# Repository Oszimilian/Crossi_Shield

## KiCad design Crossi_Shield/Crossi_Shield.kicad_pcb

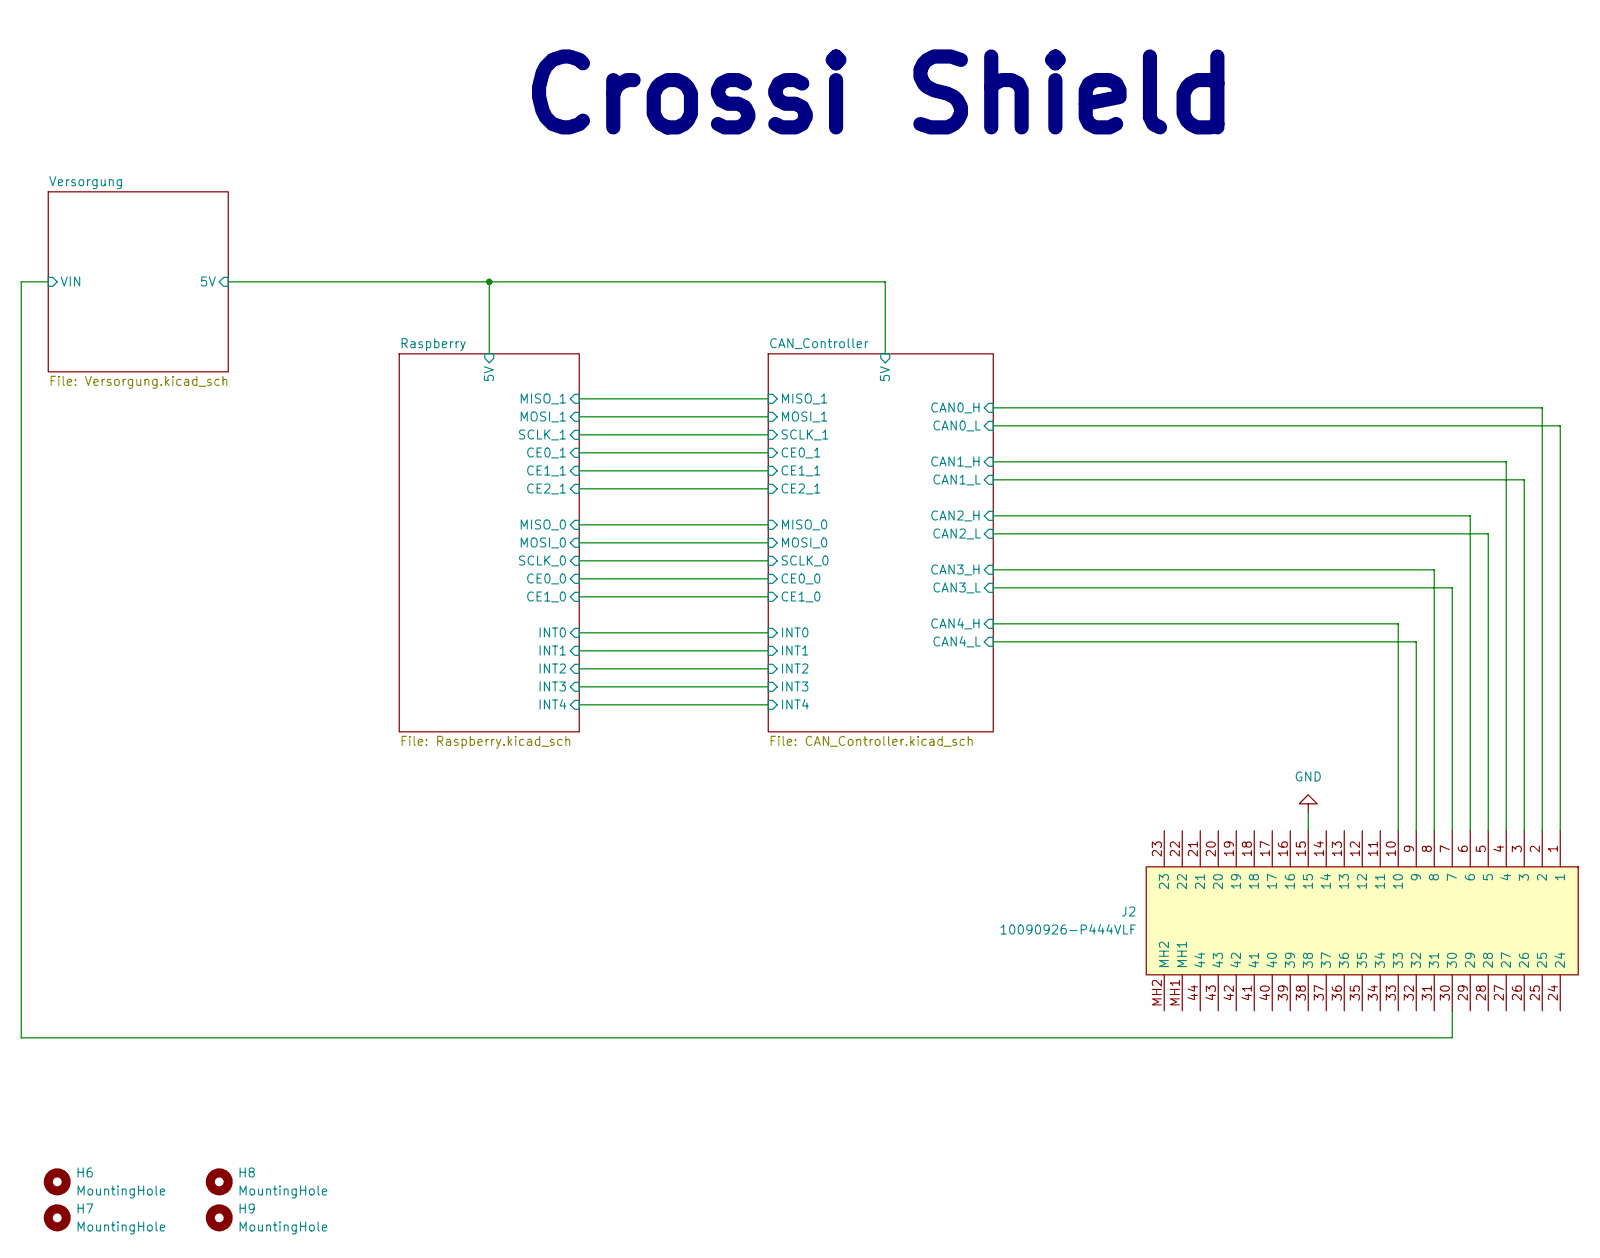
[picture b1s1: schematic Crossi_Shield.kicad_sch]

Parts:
H6, H7, H8, H9: MountingHole; MountingHole_3.2mm_M3_DIN965_Pad
J2: 10090926-P444VLF; 10090926P444VLF; Manufacturer_Part_Number 10090926-P444VLF; Mouser Part Number 649-10090926-P444VLF

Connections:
/CAN_Controller/CAN0_H: J2.2; also elsewhere on the board
/CAN_Controller/CAN0_L: J2.1; also elsewhere on the board
/CAN_Controller/CAN1_H: J2.4; also elsewhere on the board
/CAN_Controller/CAN1_L: J2.3; also elsewhere on the board
/CAN_Controller/CAN2_H: J2.6; also elsewhere on the board
/CAN_Controller/CAN2_L: J2.5; also elsewhere on the board
/CAN_Controller/CAN3_H: J2.8; also elsewhere on the board
/CAN_Controller/CAN3_L: J2.7; also elsewhere on the board
/CAN_Controller/CAN4_H: J2.10; also elsewhere on the board
/CAN_Controller/CAN4_L: J2.9; also elsewhere on the board
/Versorgung/VIN: J2.30; also elsewhere on the board
GND: J2.15; also elsewhere on the board

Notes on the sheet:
Crossi Shield

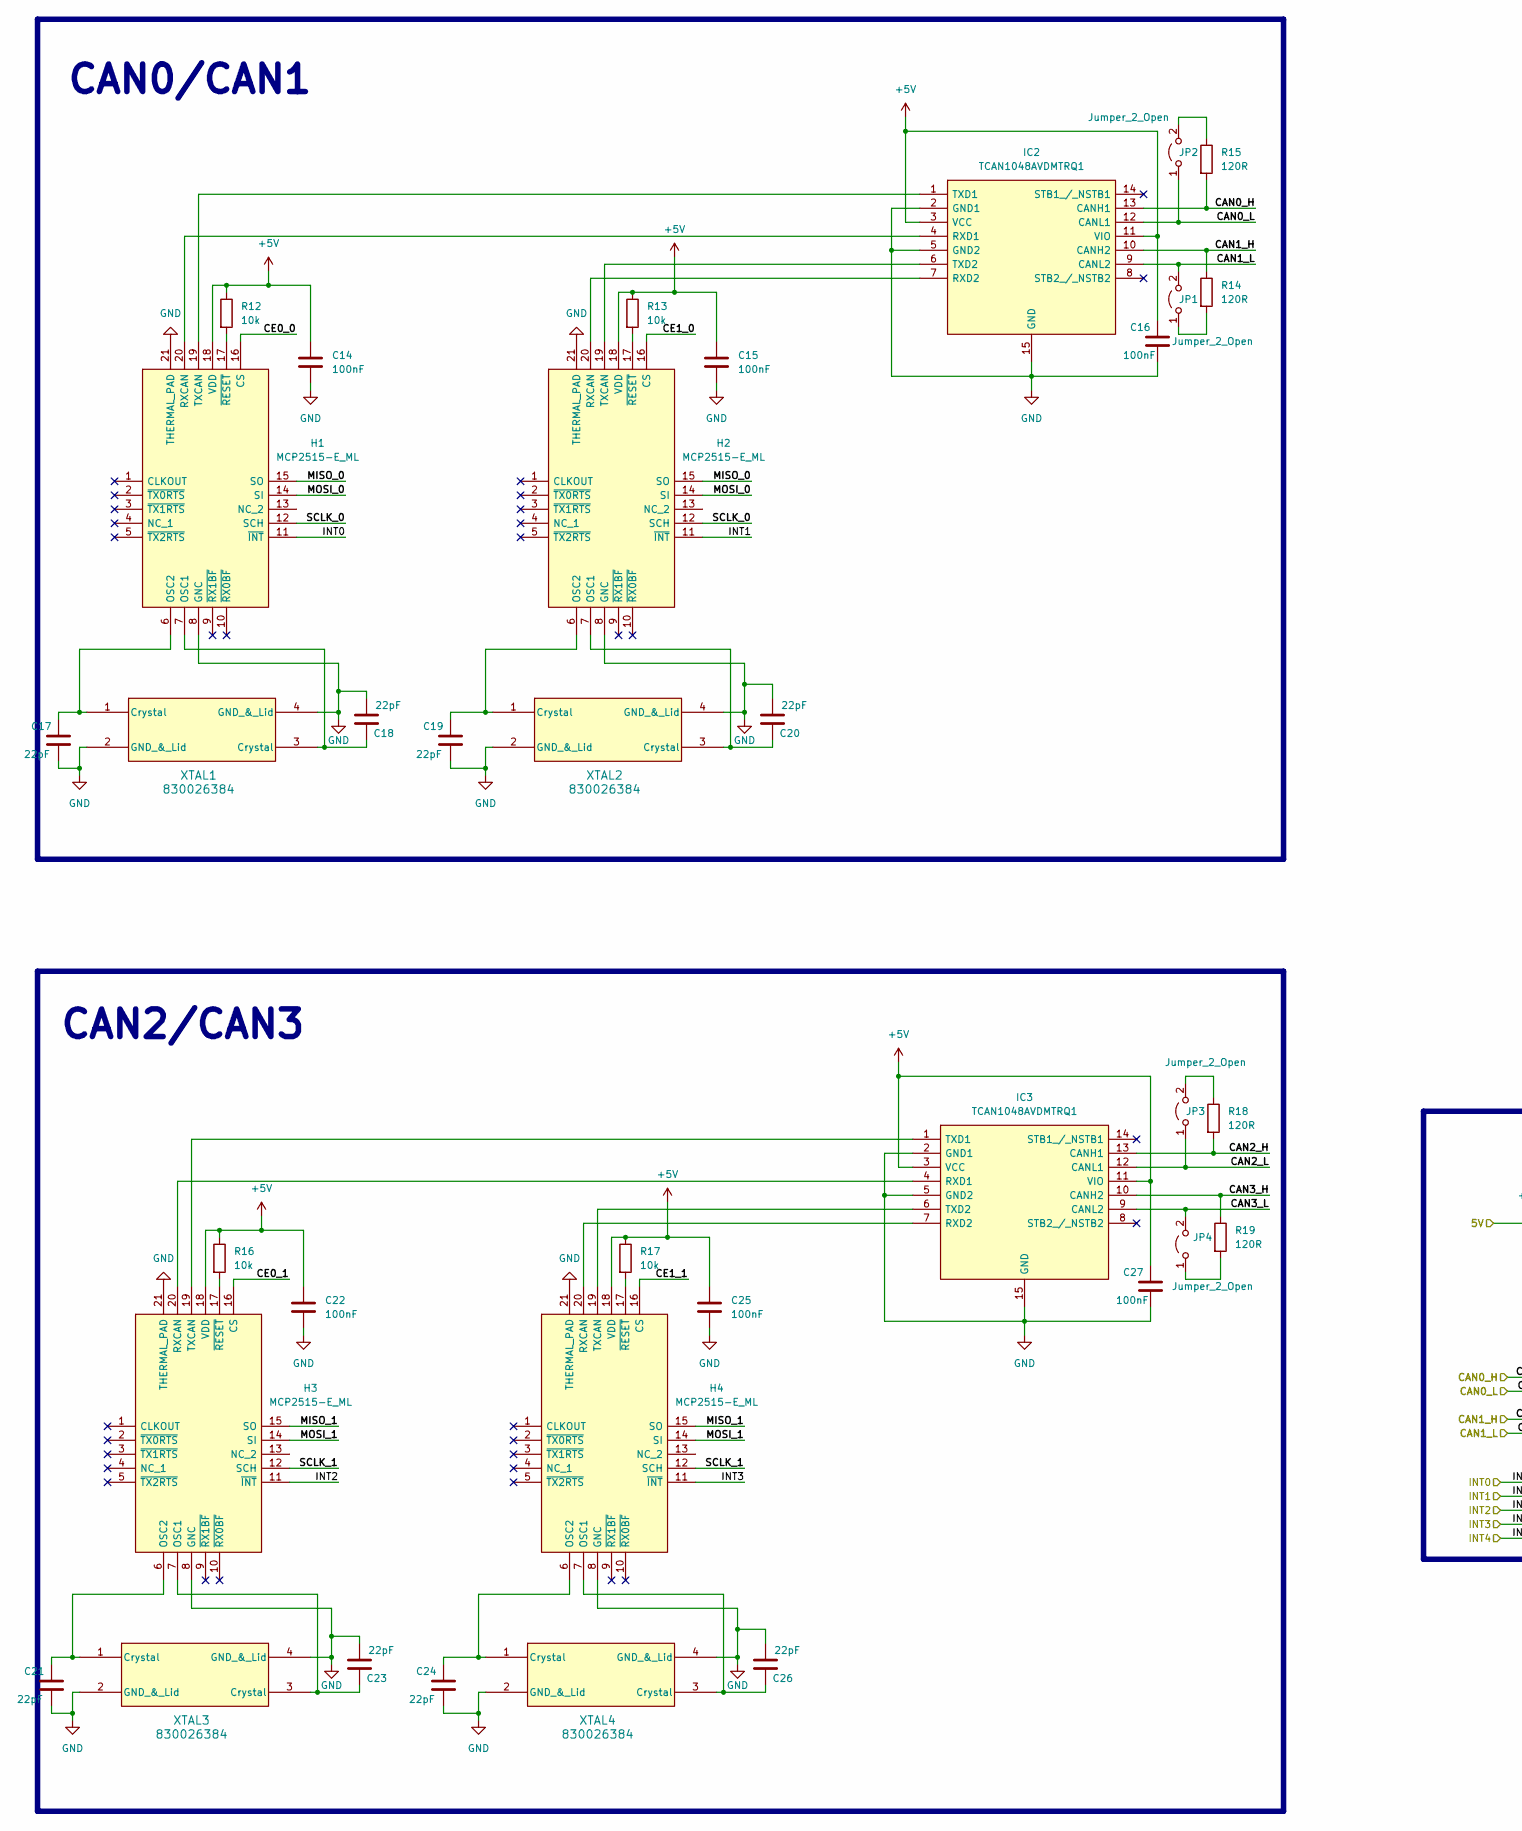
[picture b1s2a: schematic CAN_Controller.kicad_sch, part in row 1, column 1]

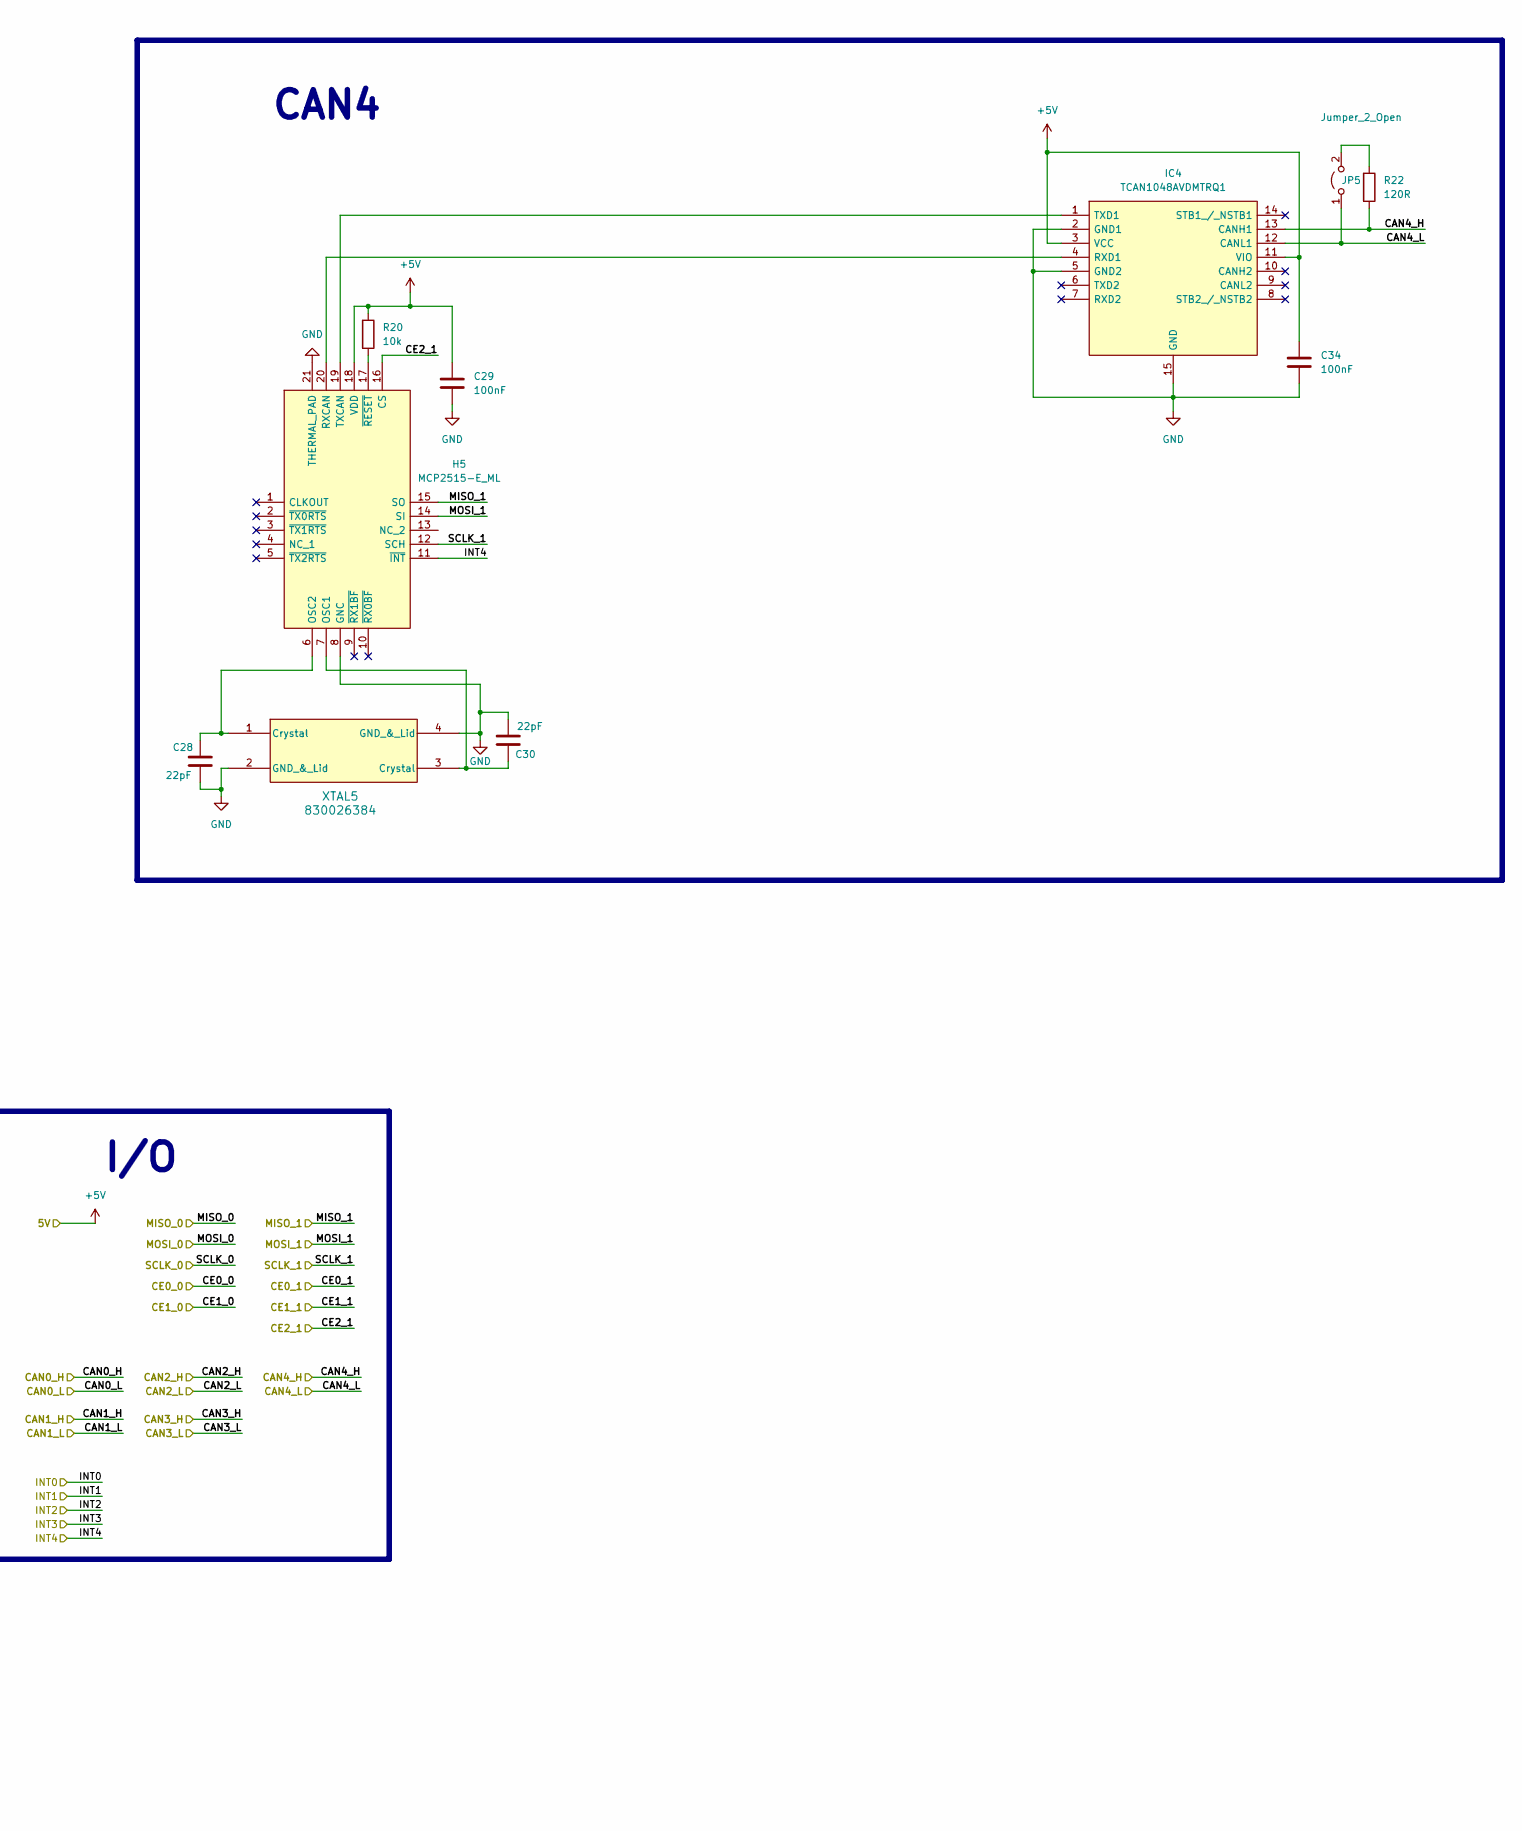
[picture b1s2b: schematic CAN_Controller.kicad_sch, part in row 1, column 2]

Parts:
C14, C15, C16, C22, C25, C27, C29, C34: 100nF; C_0805_2012Metric_Pad1.18x1.45mm_HandSolder
C17, C18, C19, C20, C21, C23, C24, C26, C28, C30: 22pF; C_0805_2012Metric_Pad1.18x1.45mm_HandSolder
H1, H2, H3, H4, H5: MCP2515-E_ML; QFN50P400X400X90-21N-D; Manufacturer_Part_Number MCP2515-E/ML; Mouser Part Number 579-MCP2515-E/ML
IC2, IC3, IC4: TCAN1048AVDMTRQ1; SON65P300X450X100-15N-D; Manufacturer_Part_Number TCAN1048AVDMTRQ1; Mouser Part Number 595-TCAN1048AVDMTRQ1
JP1, JP2, JP3, JP4, JP5: Jumper_2_Open; SolderJumper-2_P1.3mm_Open_RoundedPad1.0x1.5mm
R12, R13, R16, R17, R20: 10k; R_0805_2012Metric_Pad1.20x1.40mm_HandSolder
R14, R15, R18, R19, R22: 120R; R_0805_2012Metric_Pad1.20x1.40mm_HandSolder
XTAL1, XTAL2, XTAL3, XTAL4, XTAL5: 830026384; SMT_026384_WRE-L

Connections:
+5V: C14.1, C15.1, C16.1, C22.1, C25.1, C27.1, C29.1, C34.1, H1.18 (VDD), H2.18 (VDD), H3.18 (VDD), H4.18 (VDD), H5.18 (VDD), IC2.3 (VCC), IC2.11 (VIO), IC3.3 (VCC), IC3.11 (VIO), IC4.3 (VCC), IC4.11 (VIO), R12.1, R13.1, R16.1, R17.1, R20.1; also elsewhere on the board
/CAN_Controller/CAN0_H: IC2.13 (CANH1), R15.2; also elsewhere on the board
/CAN_Controller/CAN0_L: IC2.12 (CANL1), JP2.1 (A); also elsewhere on the board
/CAN_Controller/CAN1_H: IC2.10 (CANH2), R14.1; also elsewhere on the board
/CAN_Controller/CAN1_L: IC2.9 (CANL2), JP1.2 (B); also elsewhere on the board
/CAN_Controller/CAN2_H: IC3.13 (CANH1), R18.2; also elsewhere on the board
/CAN_Controller/CAN2_L: IC3.12 (CANL1), JP3.1 (A); also elsewhere on the board
/CAN_Controller/CAN3_H: IC3.10 (CANH2), R19.1; also elsewhere on the board
/CAN_Controller/CAN3_L: IC3.9 (CANL2), JP4.2 (B); also elsewhere on the board
/CAN_Controller/CAN4_H: IC4.13 (CANH1), R22.2; also elsewhere on the board
/CAN_Controller/CAN4_L: IC4.12 (CANL1), JP5.1 (A); also elsewhere on the board
/CAN_Controller/CE0_0: H1.16 (CS); also elsewhere on the board
/CAN_Controller/CE0_1: H3.16 (CS); also elsewhere on the board
/CAN_Controller/CE1_0: H2.16 (CS); also elsewhere on the board
/CAN_Controller/CE1_1: H4.16 (CS); also elsewhere on the board
/CAN_Controller/CE2_1: H5.16 (CS); also elsewhere on the board
/CAN_Controller/INT0: H1.11 (~INT); also elsewhere on the board
/CAN_Controller/INT1: H2.11 (~INT); also elsewhere on the board
/CAN_Controller/INT2: H3.11 (~INT); also elsewhere on the board
/CAN_Controller/INT3: H4.11 (~INT); also elsewhere on the board
/CAN_Controller/INT4: H5.11 (~INT); also elsewhere on the board
/CAN_Controller/MISO_0: H1.15 (SO), H2.15 (SO); also elsewhere on the board
/CAN_Controller/MISO_1: H3.15 (SO), H4.15 (SO), H5.15 (SO); also elsewhere on the board
/CAN_Controller/MOSI_0: H1.14 (SI), H2.14 (SI); also elsewhere on the board
/CAN_Controller/MOSI_1: H3.14 (SI), H4.14 (SI), H5.14 (SI); also elsewhere on the board
/CAN_Controller/SCLK_0: H1.12 (SCH), H2.12 (SCH); also elsewhere on the board
/CAN_Controller/SCLK_1: H3.12 (SCH), H4.12 (SCH), H5.12 (SCH); also elsewhere on the board
GND: C14.2, C15.2, C16.2, C17.2, C18.2, C19.2, C20.2, C21.2, C22.2, C23.2, C24.2, C25.2, C26.2, C27.2, C28.2, C29.2, C30.2, C34.2, H1.8 (GNC), H1.21 (THERMAL_PAD), H2.8 (GNC), H2.21 (THERMAL_PAD), H3.8 (GNC), H3.21 (THERMAL_PAD), H4.8 (GNC), H4.21 (THERMAL_PAD), H5.8 (GNC), H5.21 (THERMAL_PAD), IC2.2 (GND1), IC2.5 (GND2), IC2.15 (GND), IC3.2 (GND1), IC3.5 (GND2), IC3.15 (GND), IC4.2 (GND1), IC4.5 (GND2), IC4.15 (GND), XTAL1.2 (GND_&_Lid), XTAL1.4 (GND_&_Lid), XTAL2.2 (GND_&_Lid), XTAL2.4 (GND_&_Lid), XTAL3.2 (GND_&_Lid), XTAL3.4 (GND_&_Lid), XTAL4.2 (GND_&_Lid), XTAL4.4 (GND_&_Lid), XTAL5.2 (GND_&_Lid), XTAL5.4 (GND_&_Lid); also elsewhere on the board
unnamed: C18.1, H1.7 (OSC1), XTAL1.3 (Crystal)
unnamed: C17.1, H1.6 (OSC2), XTAL1.1 (Crystal)
unnamed: H1.20 (RXCAN), IC2.4 (RXD1)
unnamed: H1.19 (TXCAN), IC2.1 (TXD1)
unnamed: H1.17 (~RESET), R12.2
unnamed: C20.1, H2.7 (OSC1), XTAL2.3 (Crystal)
unnamed: C19.1, H2.6 (OSC2), XTAL2.1 (Crystal)
unnamed: H2.20 (RXCAN), IC2.7 (RXD2)
unnamed: H2.19 (TXCAN), IC2.6 (TXD2)
unnamed: H2.17 (~RESET), R13.2
unnamed: C23.1, H3.7 (OSC1), XTAL3.3 (Crystal)
unnamed: C21.1, H3.6 (OSC2), XTAL3.1 (Crystal)
unnamed: H3.20 (RXCAN), IC3.4 (RXD1)
unnamed: H3.19 (TXCAN), IC3.1 (TXD1)
unnamed: H3.17 (~RESET), R16.2
unnamed: C26.1, H4.7 (OSC1), XTAL4.3 (Crystal)
unnamed: C24.1, H4.6 (OSC2), XTAL4.1 (Crystal)
unnamed: H4.20 (RXCAN), IC3.7 (RXD2)
unnamed: H4.19 (TXCAN), IC3.6 (TXD2)
unnamed: H4.17 (~RESET), R17.2
unnamed: C30.1, H5.7 (OSC1), XTAL5.3 (Crystal)
unnamed: C28.1, H5.6 (OSC2), XTAL5.1 (Crystal)
unnamed: H5.20 (RXCAN), IC4.4 (RXD1)
unnamed: H5.19 (TXCAN), IC4.1 (TXD1)
unnamed: H5.17 (~RESET), R20.2
unnamed: JP1.1 (A), R14.2
unnamed: JP2.2 (B), R15.1
unnamed: JP3.2 (B), R18.1
unnamed: JP4.1 (A), R19.2
unnamed: JP5.2 (B), R22.1

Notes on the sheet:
CAN2/CAN3
CAN4
CAN0/CAN1
I/O

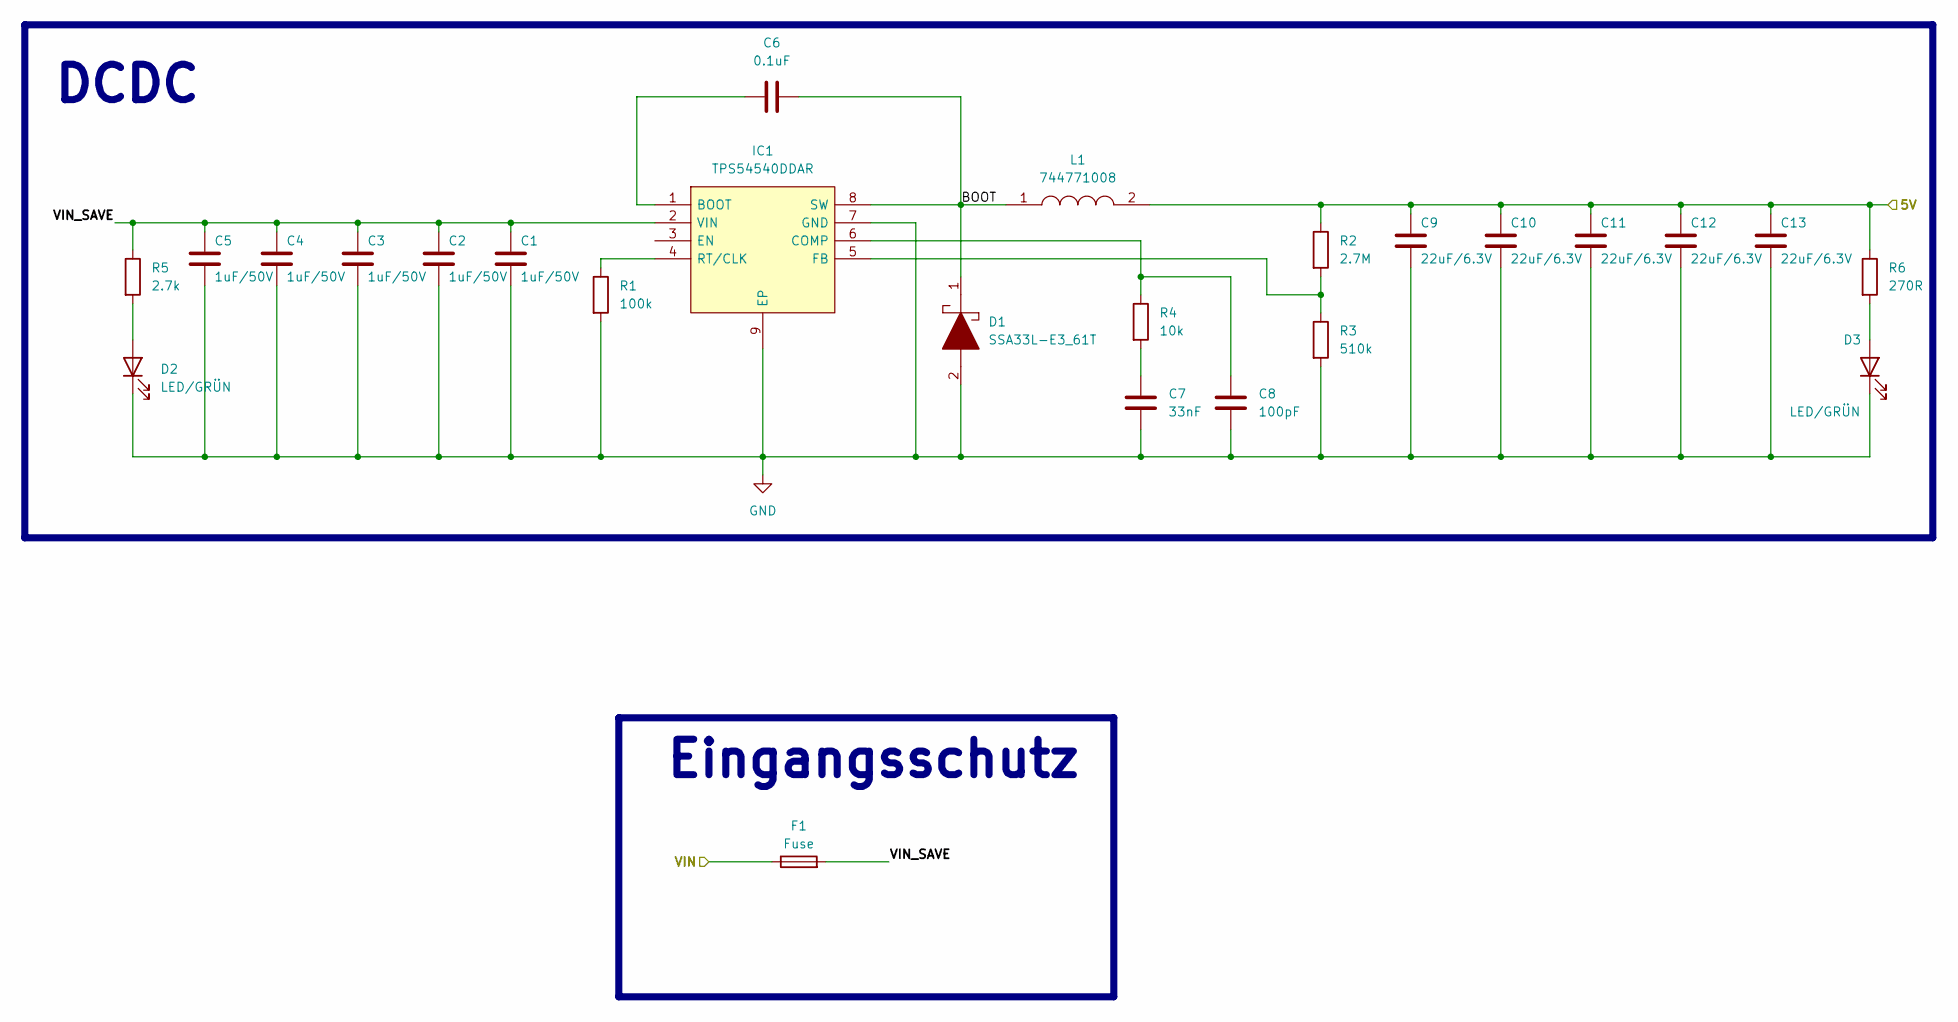
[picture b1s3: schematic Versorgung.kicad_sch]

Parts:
C1: 1uF/50V; C_0805_2012Metric_Pad1.18x1.45mm_HandSolder
C2, C3, C4, C5: 1uF/50V; R_0805_2012Metric_Pad1.20x1.40mm_HandSolder
C6: 0.1uF; C_0805_2012Metric_Pad1.18x1.45mm_HandSolder
C7: 33nF; C_0805_2012Metric_Pad1.18x1.45mm_HandSolder
C8: 100pF; C_0805_2012Metric_Pad1.18x1.45mm_HandSolder
C9, C10, C11, C12, C13: 22uF/6.3V; C_0805_2012Metric_Pad1.18x1.45mm_HandSolder
D1: SSA33L-E3_61T; DIOM5127X229N; Manufacturer_Part_Number SSA33L-E3/61T; Mouser Part Number 625-SSA33L-E3
D2, D3: LED/GRÜN; LED_0805_2012Metric_Pad1.15x1.40mm_HandSolder
F1: Fuse; R_1218_3246Metric_Pad1.22x4.75mm_HandSolder
IC1: TPS54540DDAR; SOIC127P600X170-9N; Manufacturer_Part_Number TPS54540DDAR; Mouser Part Number 595-TPS54540DDAR
L1: 744771008; WE-PD_1260_1245_1280_121054; Manufacturer_Part_Number 744771008; Mouser Part Number 710-744771008
R1: 100k; R_0805_2012Metric_Pad1.20x1.40mm_HandSolder
R2: 2.7M; R_0805_2012Metric_Pad1.20x1.40mm_HandSolder
R3: 510k; R_0805_2012Metric_Pad1.20x1.40mm_HandSolder
R4: 10k; R_0805_2012Metric_Pad1.20x1.40mm_HandSolder
R5: 2.7k; R_0805_2012Metric_Pad1.20x1.40mm_HandSolder
R6: 270R; R_0805_2012Metric_Pad1.20x1.40mm_HandSolder

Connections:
+5V: C9.1, C10.1, C11.1, C12.1, C13.1, L1.2, R2.1, R6.1; also elsewhere on the board
/Versorgung/BOOT: C6.2, D1.1, IC1.8 (SW), L1.1
/Versorgung/VIN: F1.1; also elsewhere on the board
/Versorgung/VIN_SAVE: C1.1, C2.1, C3.1, C4.1, C5.1, F1.2, IC1.2 (VIN), R5.1
GND: C1.2, C2.2, C3.2, C4.2, C5.2, C7.2, C8.2, C9.2, C10.2, C11.2, C12.2, C13.2, D1.2, D2.1 (K), D3.1 (K), IC1.7 (GND), IC1.9 (EP), R1.2, R3.2; also elsewhere on the board
unnamed: C7.1, R4.2
unnamed: D2.2 (A), R5.2
unnamed: D3.2 (A), R6.2
unnamed: C6.1, IC1.1 (BOOT)
unnamed: C8.1, IC1.6 (COMP), R4.1
unnamed: IC1.5 (FB), R2.2, R3.1
unnamed: IC1.4 (RT/CLK), R1.1

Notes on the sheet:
DCDC
Eingangsschutz

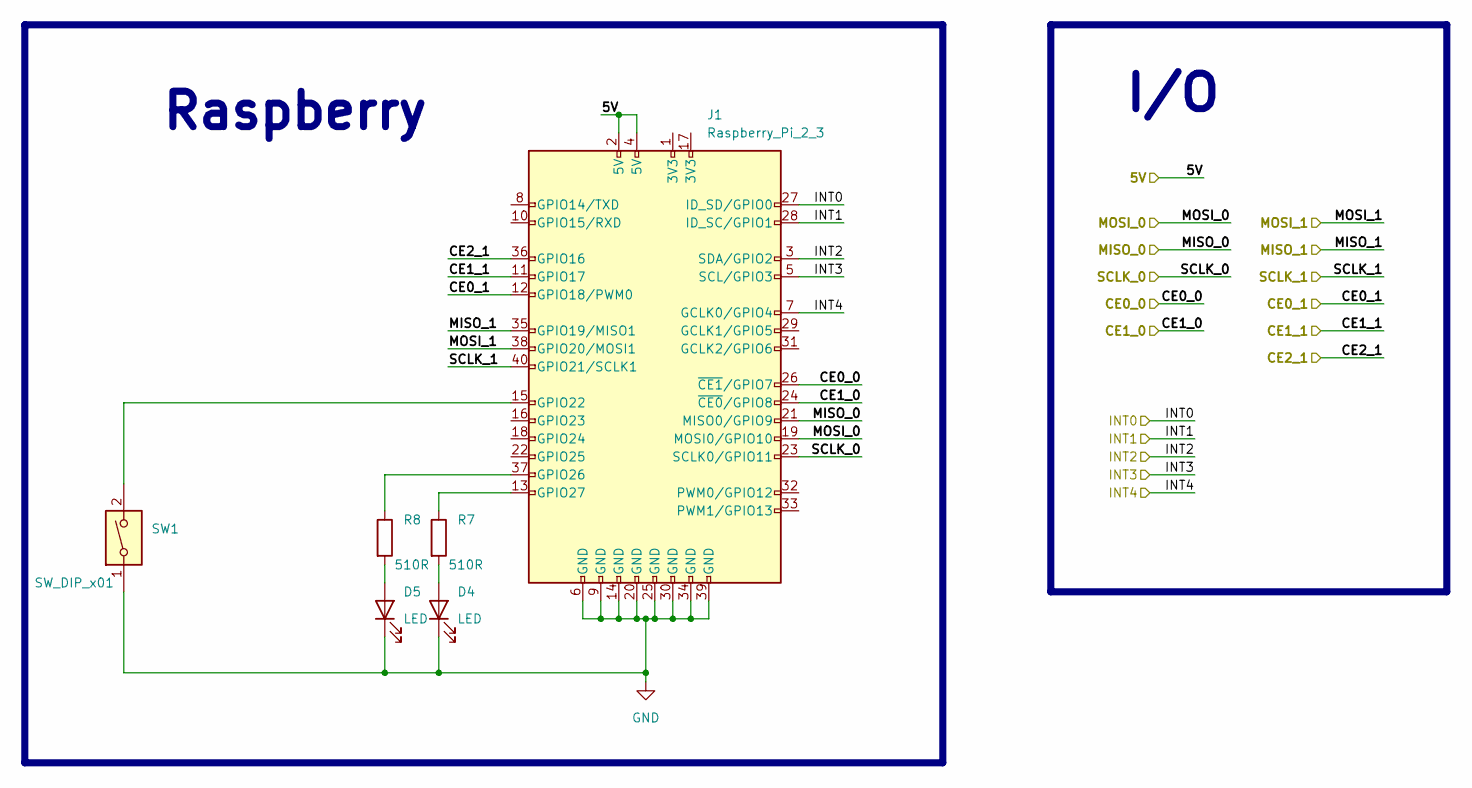
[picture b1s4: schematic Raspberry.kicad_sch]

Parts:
D4, D5: LED; LED_0805_2012Metric_Pad1.15x1.40mm_HandSolder
J1: Raspberry_Pi_2_3; PinHeader_2x20_P2.54mm_Vertical
R7, R8: 510R; R_0805_2012Metric_Pad1.20x1.40mm_HandSolder
SW1: SW_DIP_x01; SW_Push_SPST_NO_Alps_SKRK

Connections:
+5V: J1.2 (5V), J1.4 (5V); also elsewhere on the board
/CAN_Controller/CE0_0: J1.26 (~CE1/GPIO7); also elsewhere on the board
/CAN_Controller/CE0_1: J1.12 (GPIO18/PWM0); also elsewhere on the board
/CAN_Controller/CE1_0: J1.24 (~CE0/GPIO8); also elsewhere on the board
/CAN_Controller/CE1_1: J1.11 (GPIO17); also elsewhere on the board
/CAN_Controller/CE2_1: J1.36 (GPIO16); also elsewhere on the board
/CAN_Controller/INT0: J1.27 (ID_SD/GPIO0); also elsewhere on the board
/CAN_Controller/INT1: J1.28 (ID_SC/GPIO1); also elsewhere on the board
/CAN_Controller/INT2: J1.3 (SDA/GPIO2); also elsewhere on the board
/CAN_Controller/INT3: J1.5 (SCL/GPIO3); also elsewhere on the board
/CAN_Controller/INT4: J1.7 (GCLK0/GPIO4); also elsewhere on the board
/CAN_Controller/MISO_0: J1.21 (MISO0/GPIO9); also elsewhere on the board
/CAN_Controller/MISO_1: J1.35 (GPIO19/MISO1); also elsewhere on the board
/CAN_Controller/MOSI_0: J1.19 (MOSI0/GPIO10); also elsewhere on the board
/CAN_Controller/MOSI_1: J1.38 (GPIO20/MOSI1); also elsewhere on the board
/CAN_Controller/SCLK_0: J1.23 (SCLK0/GPIO11); also elsewhere on the board
/CAN_Controller/SCLK_1: J1.40 (GPIO21/SCLK1); also elsewhere on the board
GND: D4.1 (K), D5.1 (K), J1.6 (GND), J1.9 (GND), J1.14 (GND), J1.20 (GND), J1.25 (GND), J1.30 (GND), J1.34 (GND), J1.39 (GND), SW1.1; also elsewhere on the board
unnamed: D4.2 (A), R7.2
unnamed: D5.2 (A), R8.2
unnamed: J1.15 (GPIO22), SW1.2
unnamed: J1.37 (GPIO26), R8.1
unnamed: J1.13 (GPIO27), R7.1

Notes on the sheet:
Raspberry
I/O

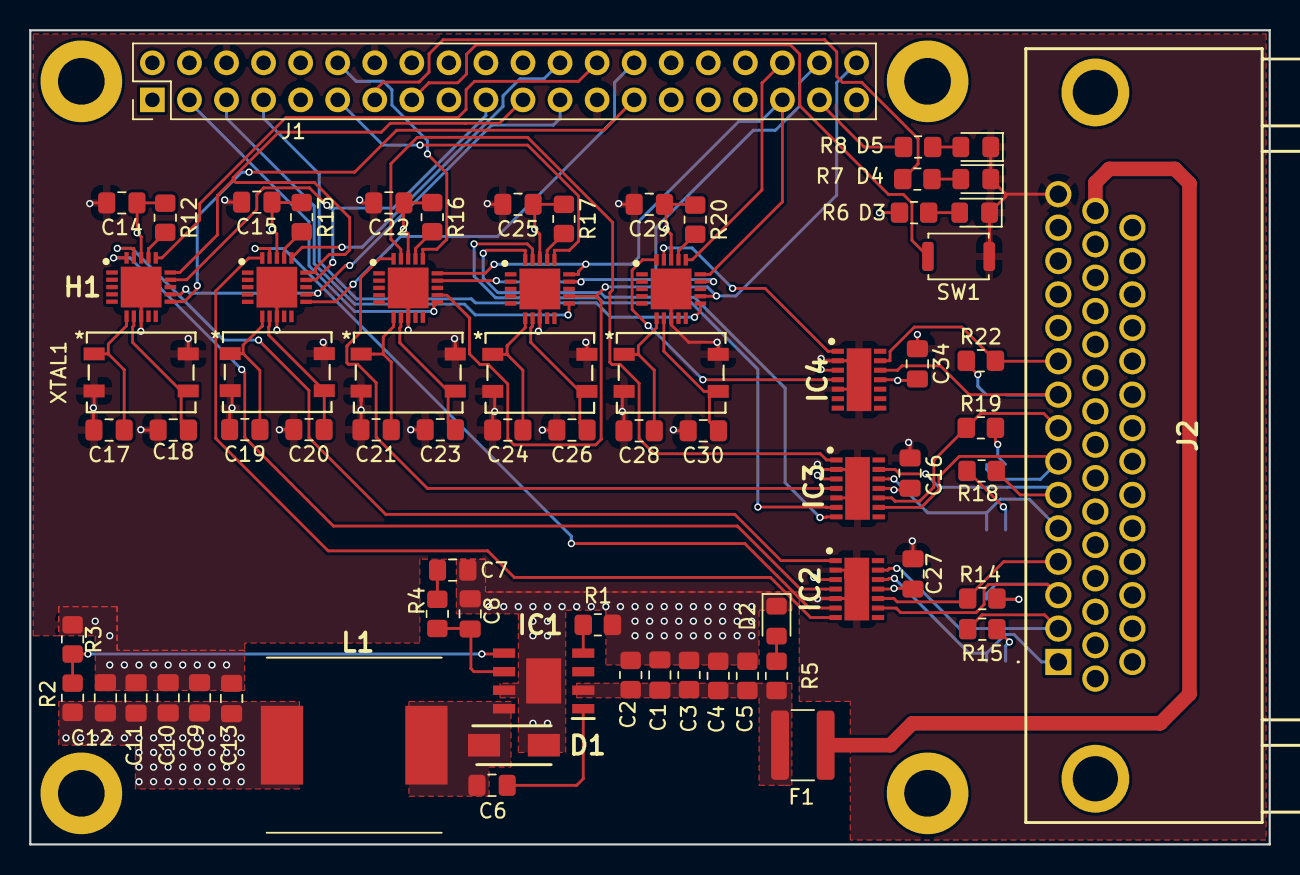
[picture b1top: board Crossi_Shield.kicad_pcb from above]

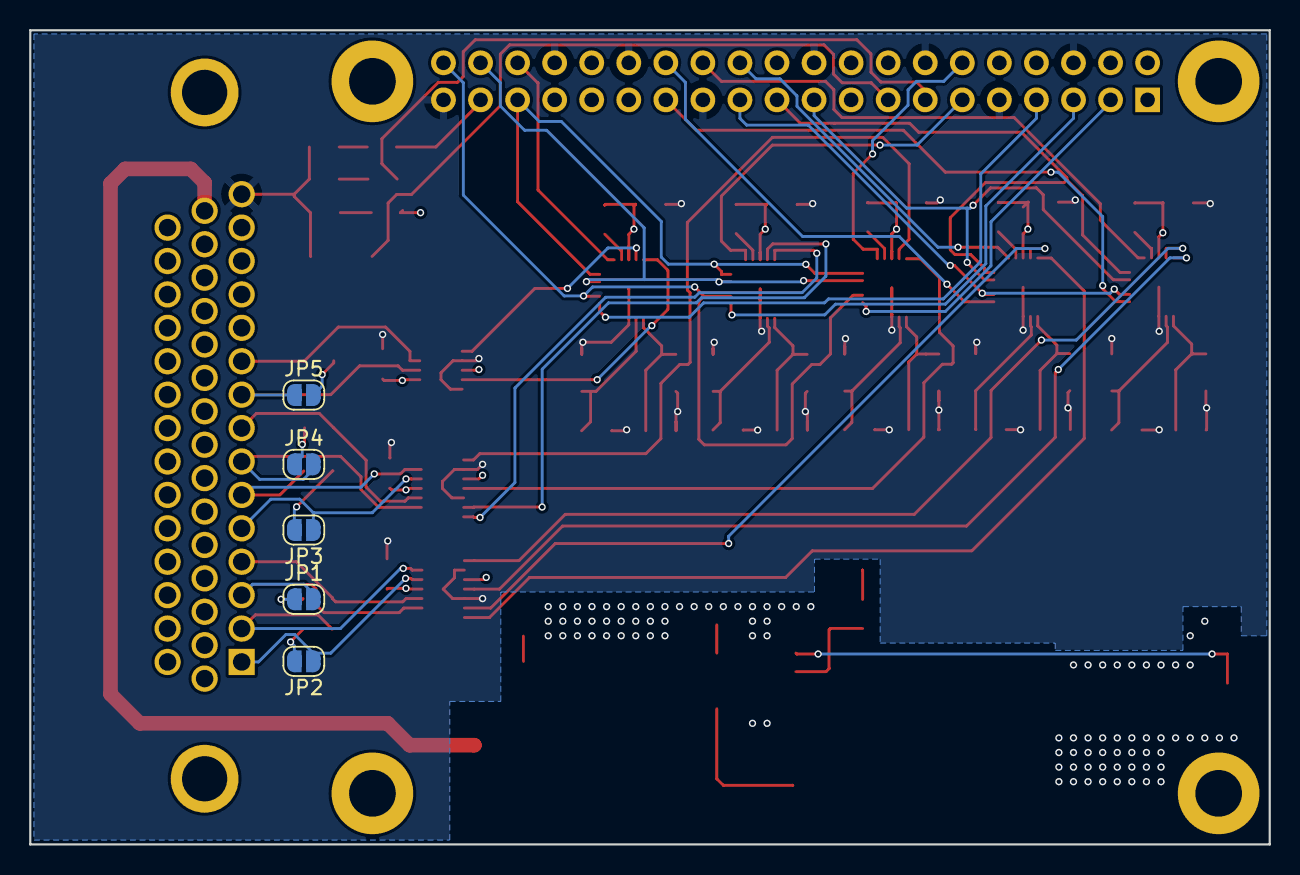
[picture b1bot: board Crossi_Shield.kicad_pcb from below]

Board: 4 copper layers, 84.9 x 55.8 mm, 82 parts (5 on the bottom side), 73 nets.

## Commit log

2023-09-15 Erster teil vom Schaltplan
2023-09-16 add 5V and gnd
2023-09-16 DSUB stecker neu
2023-09-16 Fast fertig gerouted
2023-09-17 arange device description
2023-09-17 some custom routs
2023-09-17 new buckconf design
2023-09-17 fix netlist bug and filled g&b with copper
